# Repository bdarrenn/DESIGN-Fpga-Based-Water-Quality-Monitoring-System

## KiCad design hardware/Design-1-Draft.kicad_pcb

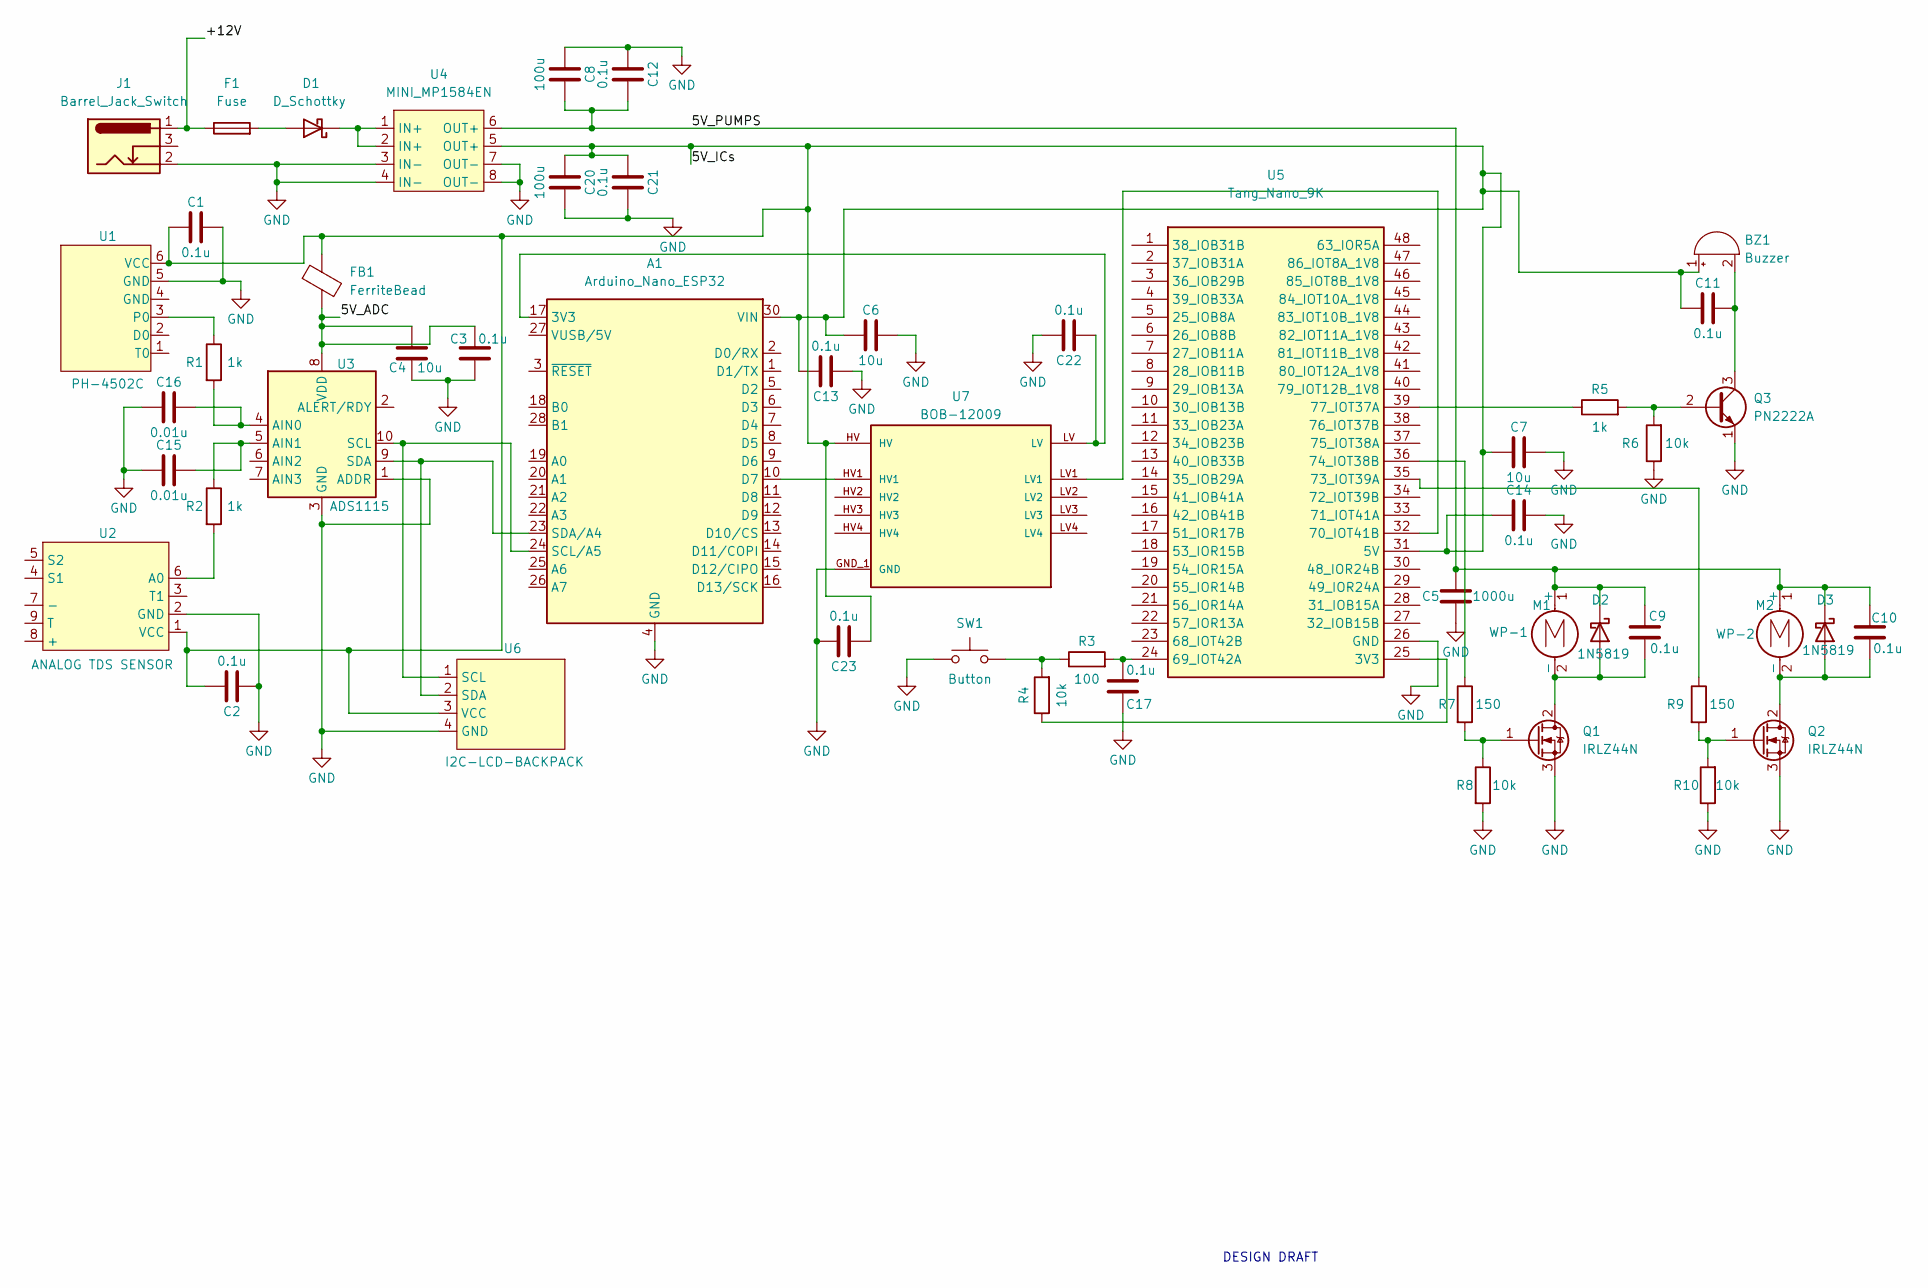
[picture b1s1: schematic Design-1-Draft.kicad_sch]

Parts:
A1: Arduino_Nano_ESP32; Arduino_Nano
BZ1: Buzzer; PinHeader_1x02_P2.54mm_Vertical
C1, C2, C3, C9, C10, C11, C12, C13, C14, C17, C21, C22, C23: 0.1u; C_Disc_D5.0mm_W2.5mm_P5.00mm
C4, C6, C7: 10u; C_Radial_D6.3mm_H5.0mm_P2.50mm
C5: 1000u; CP_Radial_D10.0mm_P5.00mm
C8, C20: 100u; C_Radial_D6.3mm_H5.0mm_P2.50mm
C15, C16: 0.01u; C_Disc_D5.0mm_W2.5mm_P5.00mm
D1: D_Schottky; D_DO-41_SOD81_P10.16mm_Horizontal
D2, D3: 1N5819; D_DO-41_SOD81_P10.16mm_Horizontal
F1: Fuse; Fuseholder_Clip-5x20mm_Keystone_3512P_Inline_P23.62x7.27mm_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
FB1: FerriteBead; R_Axial_DIN0207_L6.3mm_D2.5mm_P10.16mm_Horizontal
J1: Barrel_Jack_Switch; BarrelJack_Horizontal
M1: WP-1; PinHeader_1x02_P2.54mm_Vertical
M2: WP-2; PinHeader_1x02_P2.54mm_Vertical
Q1, Q2: IRLZ44N; TO-220-3_Vertical
Q3: PN2222A; TO-92_Inline
R1, R2, R5: 1k; R_Axial_DIN0207_L6.3mm_D2.5mm_P10.16mm_Horizontal
R3: 100; R_Axial_DIN0207_L6.3mm_D2.5mm_P10.16mm_Horizontal
R4, R6, R8, R10: 10k; R_Axial_DIN0207_L6.3mm_D2.5mm_P10.16mm_Horizontal
R7, R9: 150; R_Axial_DIN0207_L6.3mm_D2.5mm_P10.16mm_Horizontal
SW1: Button; PinHeader_1x02_P2.54mm_Vertical
U1: PH-4502C
U2: TDS-ANALOG-SENSOR
U3: ADS1115
U4: SRT_MPT1584EN_Module
U5: Tang_Nano_9K; DIP-48_TangNano9K
U6: I2C-BACKPACK-LCD
U7: BOB-12009; CONV_BOB-12009; PARTREV 01

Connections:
/5V_ADC: C3.2, C4.2, FB1.2, U3.8 (VDD)
/5V_ICs: A1.30 (VIN), BZ1.1 (+), C1.1, C2.2, C6.1, C7.1, C11.1, C13.2, C14.1, C20.1, C21.1, C23.1, FB1.1, U1.6 (VCC), U2.1 (VCC), U4.5 (OUT+), U5.31 (5V), U6.3 (VCC), U7.HV
/5V_PUMPS: C5.2, C8.2, C9.1, C10.1, C12.2, D2.1 (K), D3.1 (K), M1.1 (+), M2.1 (+), U4.6 (OUT+)
/+12V: F1.1, J1.1
GND: A1.4 (GND), A1.29 (GND), C1.2, C2.1, C3.1, C4.1, C5.1, C6.2, C7.2, C8.1, C12.1, C13.1, C14.2, C15.1, C16.1, C17.2, C20.2, C21.2, C22.2, C23.2, J1.2, Q1.3 (S), Q2.3 (S), Q3.1 (E), R6.1, R8.2, R10.1, SW1.1, U1.5 (GND), U2.2 (GND), U3.1 (ADDR), U3.3 (GND), U4.3 (IN-), U4.4 (IN-), U4.7 (OUT-), U4.8 (OUT-), U5.26 (GND), U6.4 (GND), U7.GND_1 (GND), U7.GND_2 (GND)
unnamed: A1.17 (3V3), C22.1, U7.LV
unnamed: A1.10 (D7), U7.HV1
unnamed: A1.24 (SCL/A5), U3.10 (SCL), U6.1 (SCL)
unnamed: A1.23 (SDA/A4), U3.9 (SDA), U6.2 (SDA)
unnamed: BZ1.2 (-), C11.2, Q3.3 (C)
unnamed: D1.2 (A), F1.2
unnamed: D1.1 (K), U4.1 (IN+), U4.2 (IN+)
unnamed: C9.2, D2.2 (A), M1.2 (-), Q1.2 (D)
unnamed: C10.2, D3.2 (A), M2.2 (-), Q2.2 (D)
unnamed: Q1.1 (G), R7.2, R8.1
unnamed: Q2.1 (G), R9.2, R10.2
unnamed: Q3.2 (B), R5.2, R6.2
unnamed: R3.1, R4.2, SW1.2
unnamed: R1.1, U1.3 (P0)
unnamed: R2.2, U2.6 (A0)
unnamed: C16.2, R1.2, U3.4 (AIN0)
unnamed: C15.2, R2.1, U3.5 (AIN1)
unnamed: R4.1, U5.25 (3V3)
unnamed: C17.1, R3.2, U5.24 (69_IOT42A)
unnamed: U5.32 (70_IOT41B), U7.LV1
unnamed: R9.1, U5.35 (73_IOT39A)
unnamed: R7.1, U5.36 (74_IOT38B)
unnamed: R5.1, U5.39 (77_IOT37A)

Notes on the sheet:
DESIGN DRAFT

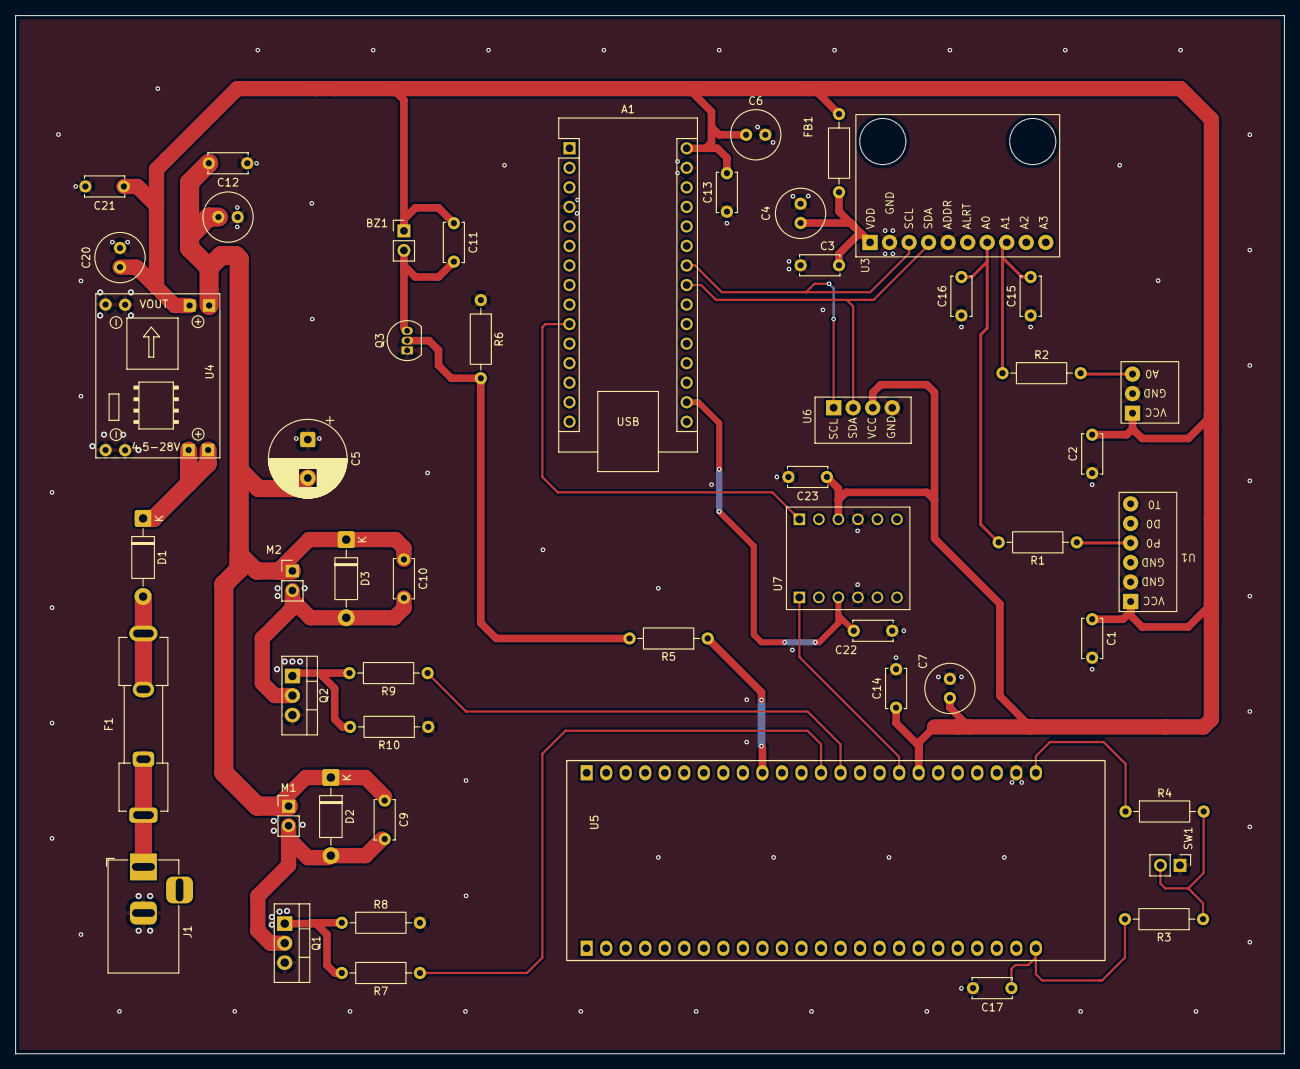
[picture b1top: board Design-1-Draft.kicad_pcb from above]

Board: 2 copper layers, 165.0 x 135.0 mm, 52 parts (0 on the bottom side), 28 nets.

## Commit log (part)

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2026-02-04 adding .gitkeep for empty folders
2026-02-04 Renaming Symbols
2026-02-04 Added Symbol and Footprint Libraries (+ yung mga custom na ginawa ko). kung ayaw maview symbols add niyo sa libraries niyo.
2026-02-05 added fuse, schottky, at adc sa pcb
2026-02-05 Assigned footprints sa schematic (kulang pa ginagawan ko pa yung iba)
2026-02-05 added footprints to pcb (not yet complete)
2026-02-06 updated footprint lib
2026-02-06 updated footprints
2026-02-06 some updates footprint and pcb
2026-02-07 updated custom footprints
2026-02-08 Updated Footprint Library for custom footprints. Fixed PCB footprints, traces nalang kulang
2026-02-08 realigned some footprints, figuring out trace paths
2026-02-08 fixed footprint text
2026-02-08 added some traces
2026-02-09 updated schematic and pcb
2026-02-10 updated pcb
2026-02-10 updated PCB and footprint lib
2026-02-10 updated PCB (fixed some trace angles)
2026-02-10 updated pcb (added top and bottom GND pour, hide nalang kung may gustong iedit
2026-02-10 updated PCB (added vias for ground pours)
2026-02-10 updated PCB, ground pour and vias
2026-06-05 modified schem, wala pang pcb
2026-06-06 added arduino code
2026-06-11 schem and symbols/footprint for shifter
2026-06-17 revised schem, renamed GND symbols > GND zones, removed buck converter, 5V to arduino & adc
2026-06-17 schem: buck converter added > one ground plane pcb: NEW component placement, need traces and ground fills
2026-06-17 updated pcb, traces & ground fills pa
2026-06-17 updated PCB, traces and ground fills pa
2026-06-18 Updated PCB & SCHEM
2026-06-19 updated schem (added multiple caps & 2 flyback diodes @pumps)
2026-06-19 adding logic shifter footprint
2026-06-26 Updated PCB and Schem
